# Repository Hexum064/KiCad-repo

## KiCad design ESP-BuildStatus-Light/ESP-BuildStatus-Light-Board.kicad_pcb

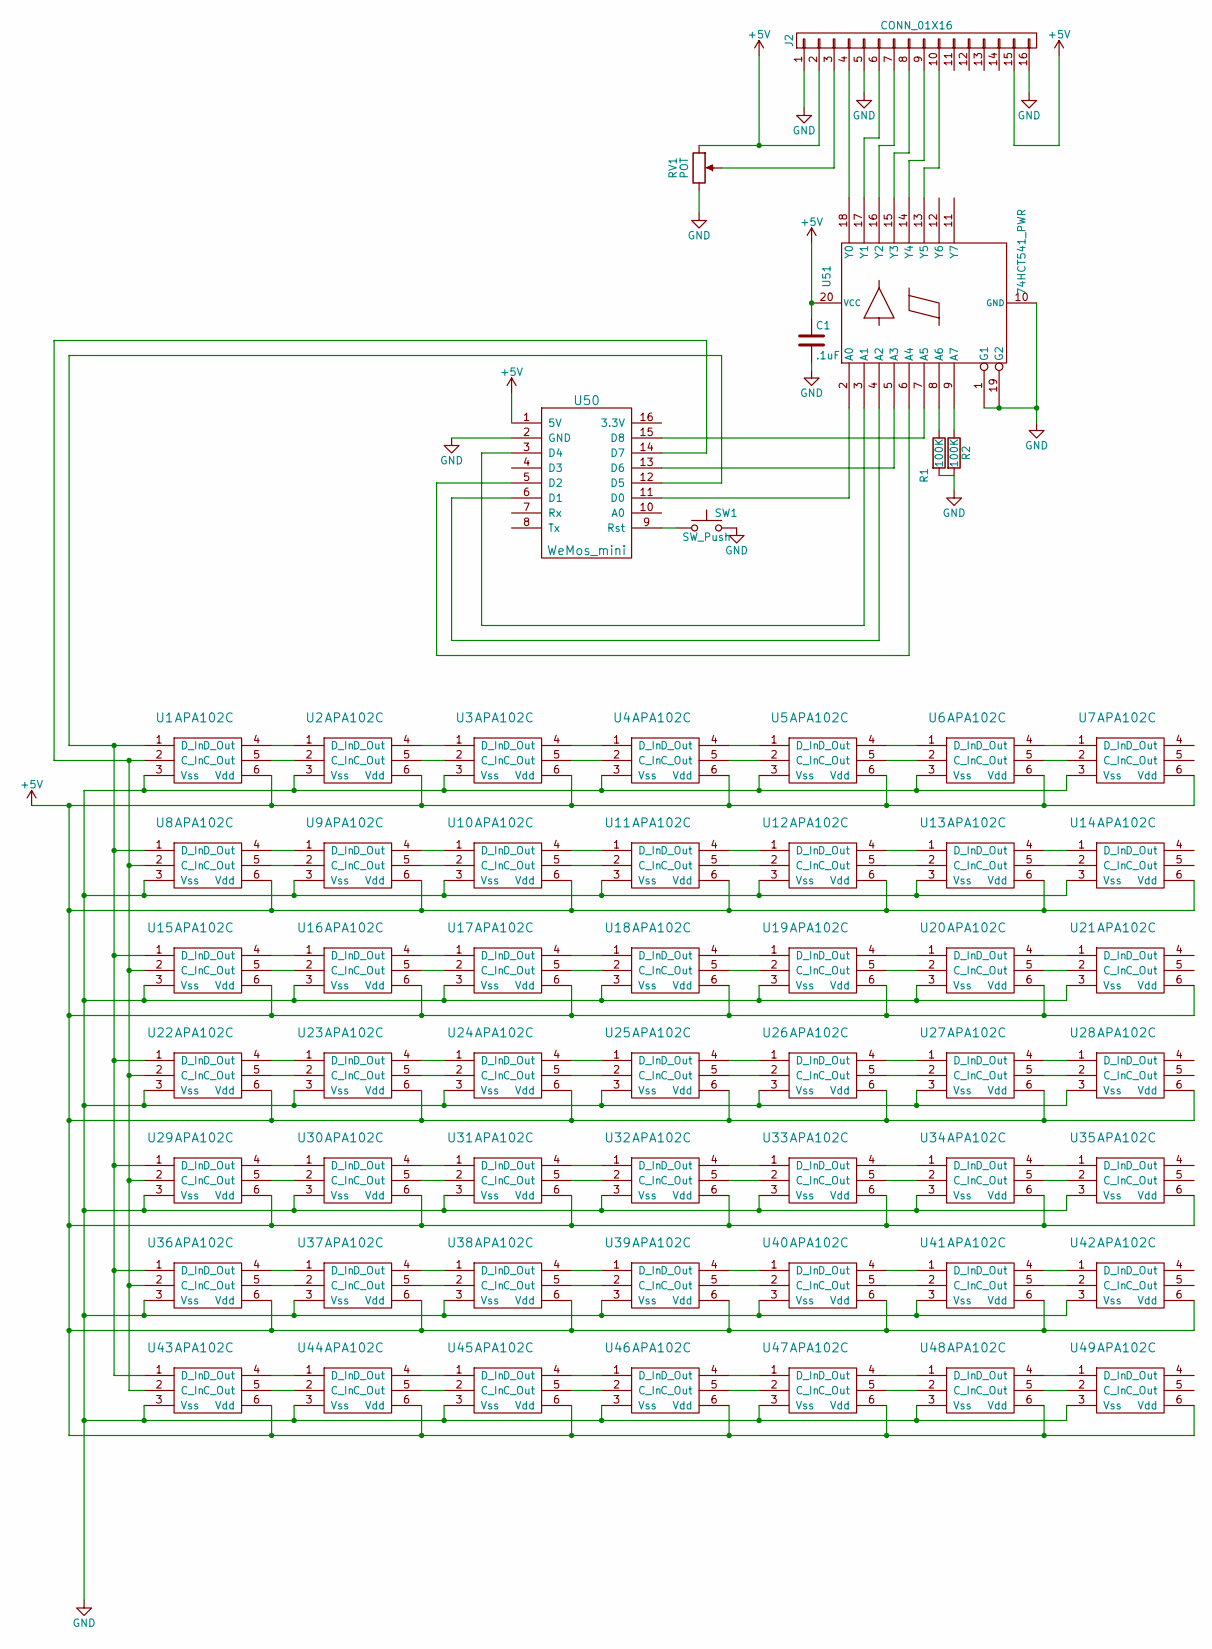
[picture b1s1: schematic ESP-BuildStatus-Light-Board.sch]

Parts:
C1: .1uF; C_0603_HandSoldering
J2: CONN_01X16; Socket_Strip_Angled_1x16_Pitch2.54mm
R1, R2: 100K; R_0603_HandSoldering
RV1: POT; Potentiometer_Triwood_RM-065
SW1: SW_Push; SW_PUSH_6mm_h5mm
U1, U2, U3, U4, U5, U6, U7, U8, U9, U10, U11, U12, U13, U14, U15, U16, U17, U18, U19, U20, U21, U22, U23, U24, U25, U26, U27, U28, U29, U30, U31, U32, U33, U34, U35, U36, U37, U38, U39, U40, U41, U42, U43, U44, U45, U46, U47, U48, U49: APA102C; LED_RGB_5050-6
U50: WeMos_mini; D1_mini_board_smd
U51: 74HCT541_PWR; TSSOP20

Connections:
GND: C1.2, J2.1, J2.5, J2.16, R1.2, R2.2, RV1.3, SW1.2, U1.3 (Vss), U2.3 (Vss), U3.3 (Vss), U4.3 (Vss), U5.3 (Vss), U6.3 (Vss), U7.3 (Vss), U8.3 (Vss), U9.3 (Vss), U10.3 (Vss), U11.3 (Vss), U12.3 (Vss), U13.3 (Vss), U14.3 (Vss), U15.3 (Vss), U16.3 (Vss), U17.3 (Vss), U18.3 (Vss), U19.3 (Vss), U20.3 (Vss), U21.3 (Vss), U22.3 (Vss), U23.3 (Vss), U24.3 (Vss), U25.3 (Vss), U26.3 (Vss), U27.3 (Vss), U28.3 (Vss), U29.3 (Vss), U30.3 (Vss), U31.3 (Vss), U32.3 (Vss), U33.3 (Vss), U34.3 (Vss), U35.3 (Vss), U36.3 (Vss), U37.3 (Vss), U38.3 (Vss), U39.3 (Vss), U40.3 (Vss), U41.3 (Vss), U42.3 (Vss), U43.3 (Vss), U44.3 (Vss), U45.3 (Vss), U46.3 (Vss), U47.3 (Vss), U48.3 (Vss), U49.3 (Vss), U50.2 (GND), U51.1 (G1), U51.10 (GND), U51.19 (G2)
unnamed: J2.3, RV1.2
unnamed: J2.4, U51.18 (Y0)
unnamed: J2.6, U51.17 (Y1)
unnamed: J2.7, U51.16 (Y2)
unnamed: J2.8, U51.15 (Y3)
unnamed: J2.9, U51.14 (Y4)
unnamed: J2.10, U51.13 (Y5)
unnamed: R1.1, U51.8 (A6)
unnamed: R2.1, U51.9 (A7)
unnamed: SW1.1, U50.9 (Rst)
unnamed: U1.1 (D_In), U8.1 (D_In), U15.1 (D_In), U22.1 (D_In), U29.1 (D_In), U36.1 (D_In), U43.1 (D_In), U50.12 (D5)
unnamed: U1.2 (C_In), U8.2 (C_In), U15.2 (C_In), U22.2 (C_In), U29.2 (C_In), U36.2 (C_In), U43.2 (C_In), U50.14 (D7)
unnamed: U1.4 (D_Out), U2.1 (D_In)
unnamed: U1.5 (C_Out), U2.2 (C_In)
unnamed: U2.4 (D_Out), U3.1 (D_In)
unnamed: U2.5 (C_Out), U3.2 (C_In)
unnamed: U3.4 (D_Out), U4.1 (D_In)
unnamed: U3.5 (C_Out), U4.2 (C_In)
unnamed: U4.4 (D_Out), U5.1 (D_In)
unnamed: U4.5 (C_Out), U5.2 (C_In)
unnamed: U5.4 (D_Out), U6.1 (D_In)
unnamed: U5.5 (C_Out), U6.2 (C_In)
unnamed: U6.4 (D_Out), U7.1 (D_In)
unnamed: U6.5 (C_Out), U7.2 (C_In)
unnamed: U8.4 (D_Out), U9.1 (D_In)
unnamed: U8.5 (C_Out), U9.2 (C_In)
unnamed: U9.4 (D_Out), U10.1 (D_In)
unnamed: U9.5 (C_Out), U10.2 (C_In)
unnamed: U10.4 (D_Out), U11.1 (D_In)
unnamed: U10.5 (C_Out), U11.2 (C_In)
unnamed: U11.4 (D_Out), U12.1 (D_In)
unnamed: U11.5 (C_Out), U12.2 (C_In)
unnamed: U12.4 (D_Out), U13.1 (D_In)
unnamed: U12.5 (C_Out), U13.2 (C_In)
unnamed: U13.4 (D_Out), U14.1 (D_In)
unnamed: U13.5 (C_Out), U14.2 (C_In)
unnamed: U15.4 (D_Out), U16.1 (D_In)
unnamed: U15.5 (C_Out), U16.2 (C_In)
unnamed: U16.4 (D_Out), U17.1 (D_In)
unnamed: U16.5 (C_Out), U17.2 (C_In)
unnamed: U17.4 (D_Out), U18.1 (D_In)
unnamed: U17.5 (C_Out), U18.2 (C_In)
unnamed: U18.4 (D_Out), U19.1 (D_In)
unnamed: U18.5 (C_Out), U19.2 (C_In)
unnamed: U19.4 (D_Out), U20.1 (D_In)
unnamed: U19.5 (C_Out), U20.2 (C_In)
unnamed: U20.4 (D_Out), U21.1 (D_In)
unnamed: U20.5 (C_Out), U21.2 (C_In)
unnamed: U22.4 (D_Out), U23.1 (D_In)
unnamed: U22.5 (C_Out), U23.2 (C_In)
unnamed: U23.4 (D_Out), U24.1 (D_In)
unnamed: U23.5 (C_Out), U24.2 (C_In)
unnamed: U24.4 (D_Out), U25.1 (D_In)
unnamed: U24.5 (C_Out), U25.2 (C_In)
unnamed: U25.4 (D_Out), U26.1 (D_In)
unnamed: U25.5 (C_Out), U26.2 (C_In)
unnamed: U26.4 (D_Out), U27.1 (D_In)
unnamed: U26.5 (C_Out), U27.2 (C_In)
unnamed: U27.4 (D_Out), U28.1 (D_In)
unnamed: U27.5 (C_Out), U28.2 (C_In)
unnamed: U29.4 (D_Out), U30.1 (D_In)
unnamed: U29.5 (C_Out), U30.2 (C_In)
unnamed: U30.4 (D_Out), U31.1 (D_In)
unnamed: U30.5 (C_Out), U31.2 (C_In)
unnamed: U31.4 (D_Out), U32.1 (D_In)
unnamed: U31.5 (C_Out), U32.2 (C_In)
unnamed: U32.4 (D_Out), U33.1 (D_In)
unnamed: U32.5 (C_Out), U33.2 (C_In)
unnamed: U33.4 (D_Out), U34.1 (D_In)
unnamed: U33.5 (C_Out), U34.2 (C_In)
unnamed: U34.4 (D_Out), U35.1 (D_In)
unnamed: U34.5 (C_Out), U35.2 (C_In)
unnamed: U36.4 (D_Out), U37.1 (D_In)
unnamed: U36.5 (C_Out), U37.2 (C_In)
unnamed: U37.4 (D_Out), U38.1 (D_In)
unnamed: U37.5 (C_Out), U38.2 (C_In)
unnamed: U38.4 (D_Out), U39.1 (D_In)
unnamed: U38.5 (C_Out), U39.2 (C_In)
unnamed: U39.4 (D_Out), U40.1 (D_In)
unnamed: U39.5 (C_Out), U40.2 (C_In)
unnamed: U40.4 (D_Out), U41.1 (D_In)
unnamed: U40.5 (C_Out), U41.2 (C_In)
unnamed: U41.4 (D_Out), U42.1 (D_In)
unnamed: U41.5 (C_Out), U42.2 (C_In)
unnamed: U43.4 (D_Out), U44.1 (D_In)
unnamed: U43.5 (C_Out), U44.2 (C_In)
unnamed: U44.4 (D_Out), U45.1 (D_In)
unnamed: U44.5 (C_Out), U45.2 (C_In)
unnamed: U45.4 (D_Out), U46.1 (D_In)
unnamed: U45.5 (C_Out), U46.2 (C_In)
unnamed: U46.4 (D_Out), U47.1 (D_In)
unnamed: U46.5 (C_Out), U47.2 (C_In)
unnamed: U47.4 (D_Out), U48.1 (D_In)
unnamed: U47.5 (C_Out), U48.2 (C_In)
unnamed: U48.4 (D_Out), U49.1 (D_In)
unnamed: U48.5 (C_Out), U49.2 (C_In)
unnamed: U50.3 (D4), U51.3 (A1)
unnamed: U50.5 (D2), U51.6 (A4)
unnamed: U50.6 (D1), U51.4 (A2)
unnamed: U50.11 (D0), U51.2 (A0)
unnamed: U50.13 (D6), U51.5 (A3)
unnamed: U50.15 (D8), U51.7 (A5)

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
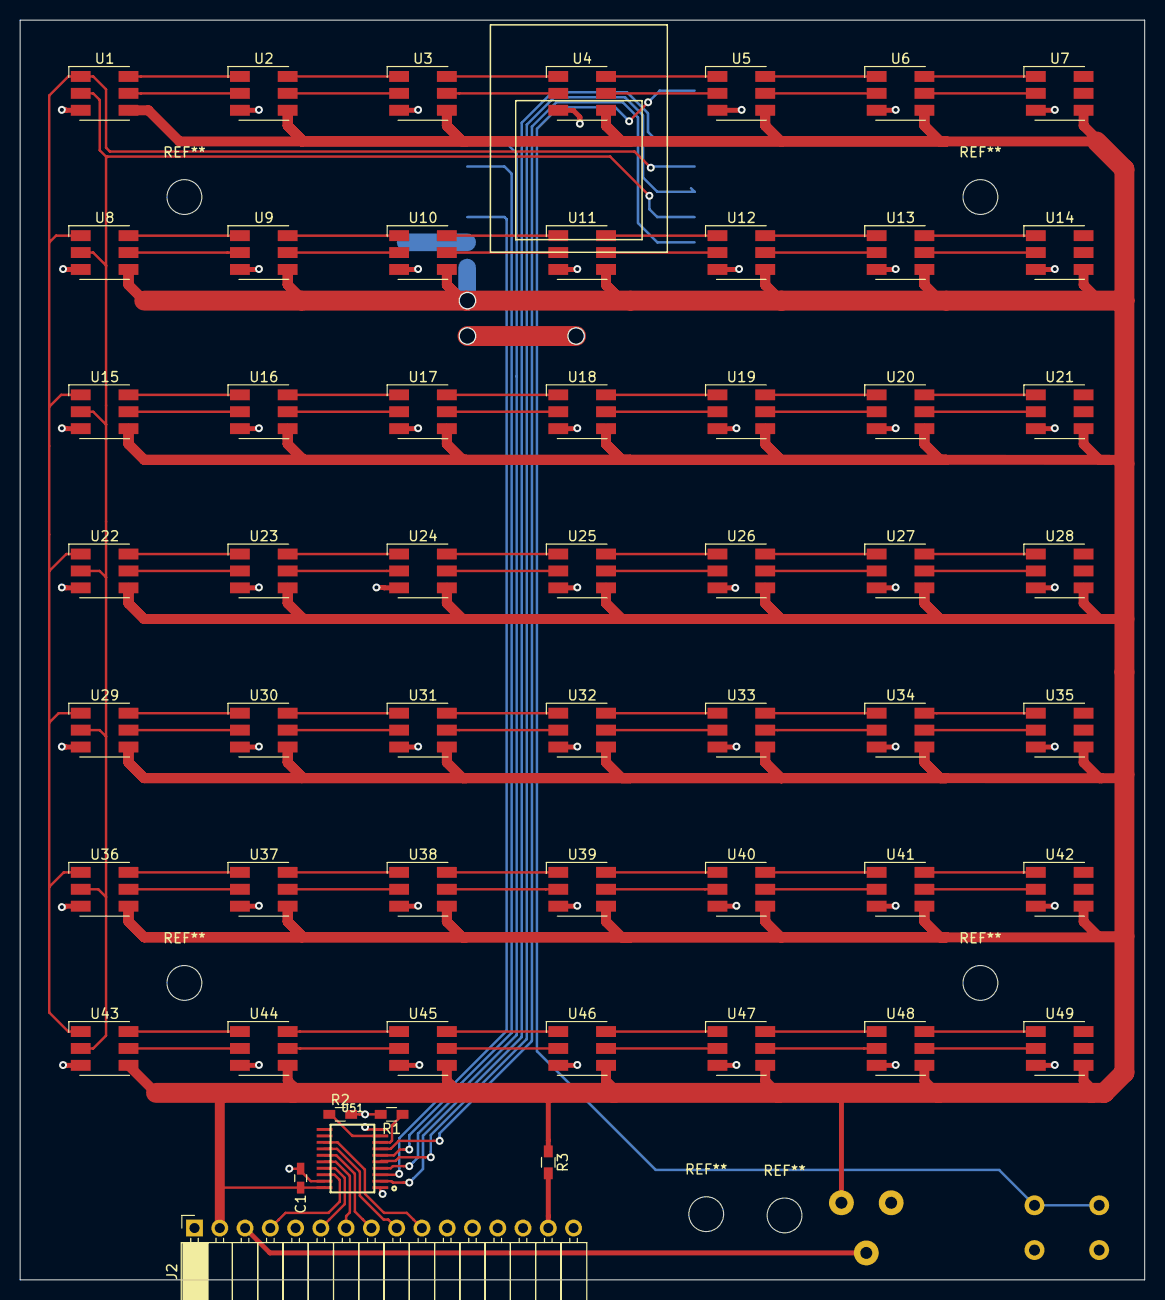
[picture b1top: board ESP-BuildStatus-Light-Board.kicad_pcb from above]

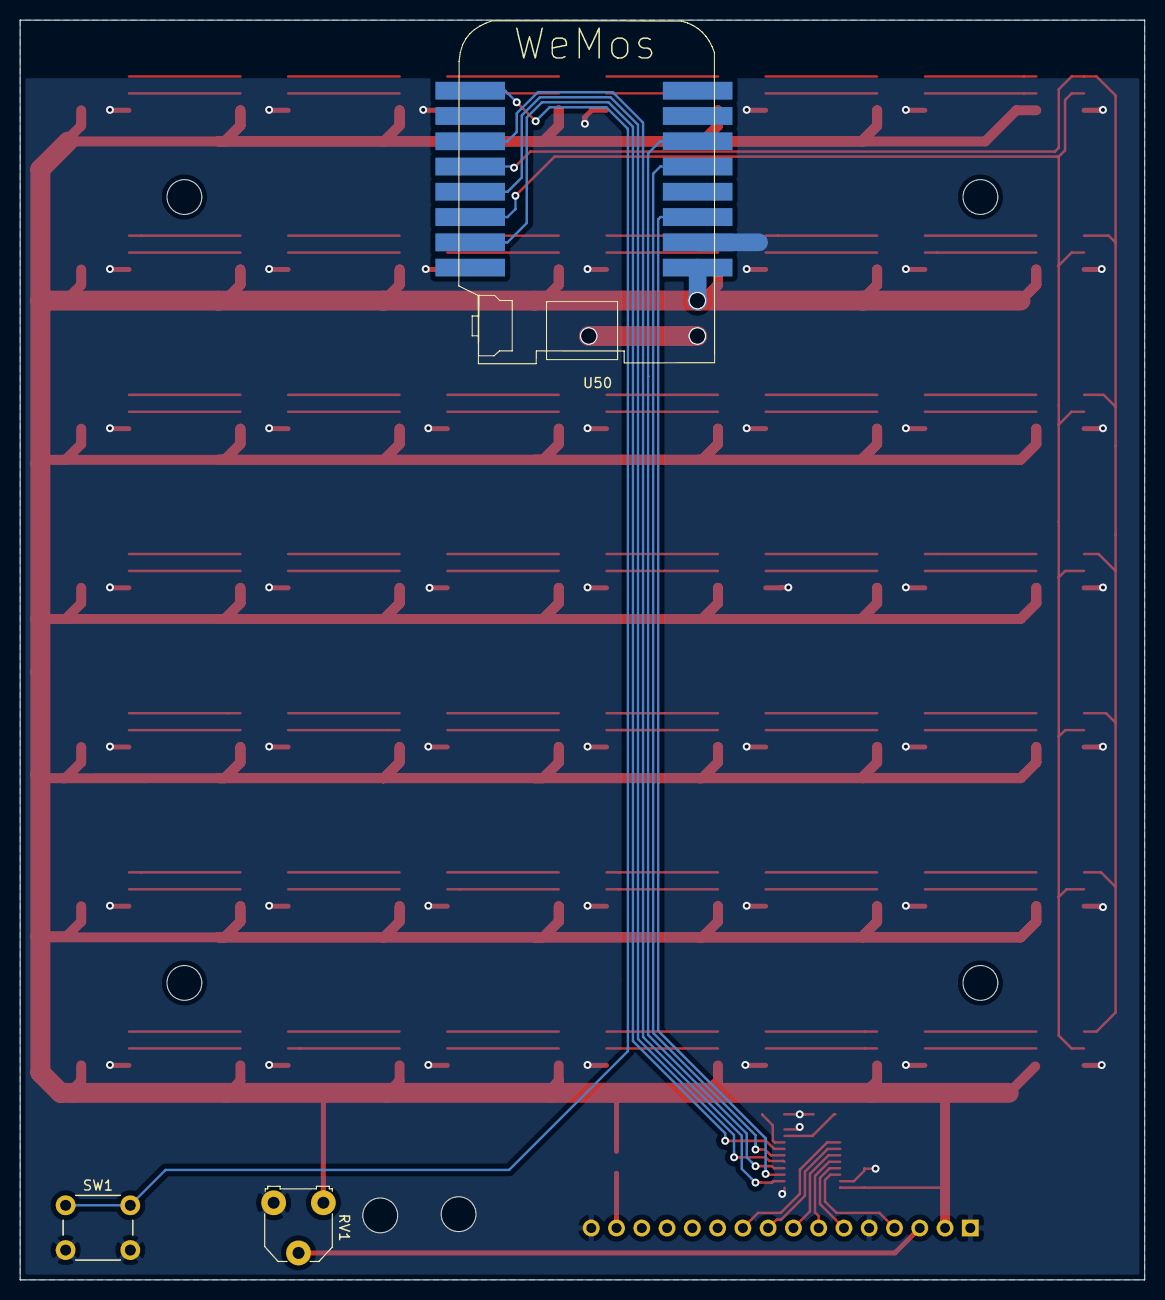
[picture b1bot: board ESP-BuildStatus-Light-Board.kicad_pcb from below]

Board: 2 copper layers, 113.0 x 126.6 mm, 58 parts (3 on the bottom side), 105 nets.

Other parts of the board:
R3: 1K; R_0603_HandSoldering

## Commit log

2020-02-07 Modified traces from WeMos to Level Shifter
2020-02-10 Updated the traces between ESP and LCD for better grounding
2020-03-23 fixed problems with circuit and board design
